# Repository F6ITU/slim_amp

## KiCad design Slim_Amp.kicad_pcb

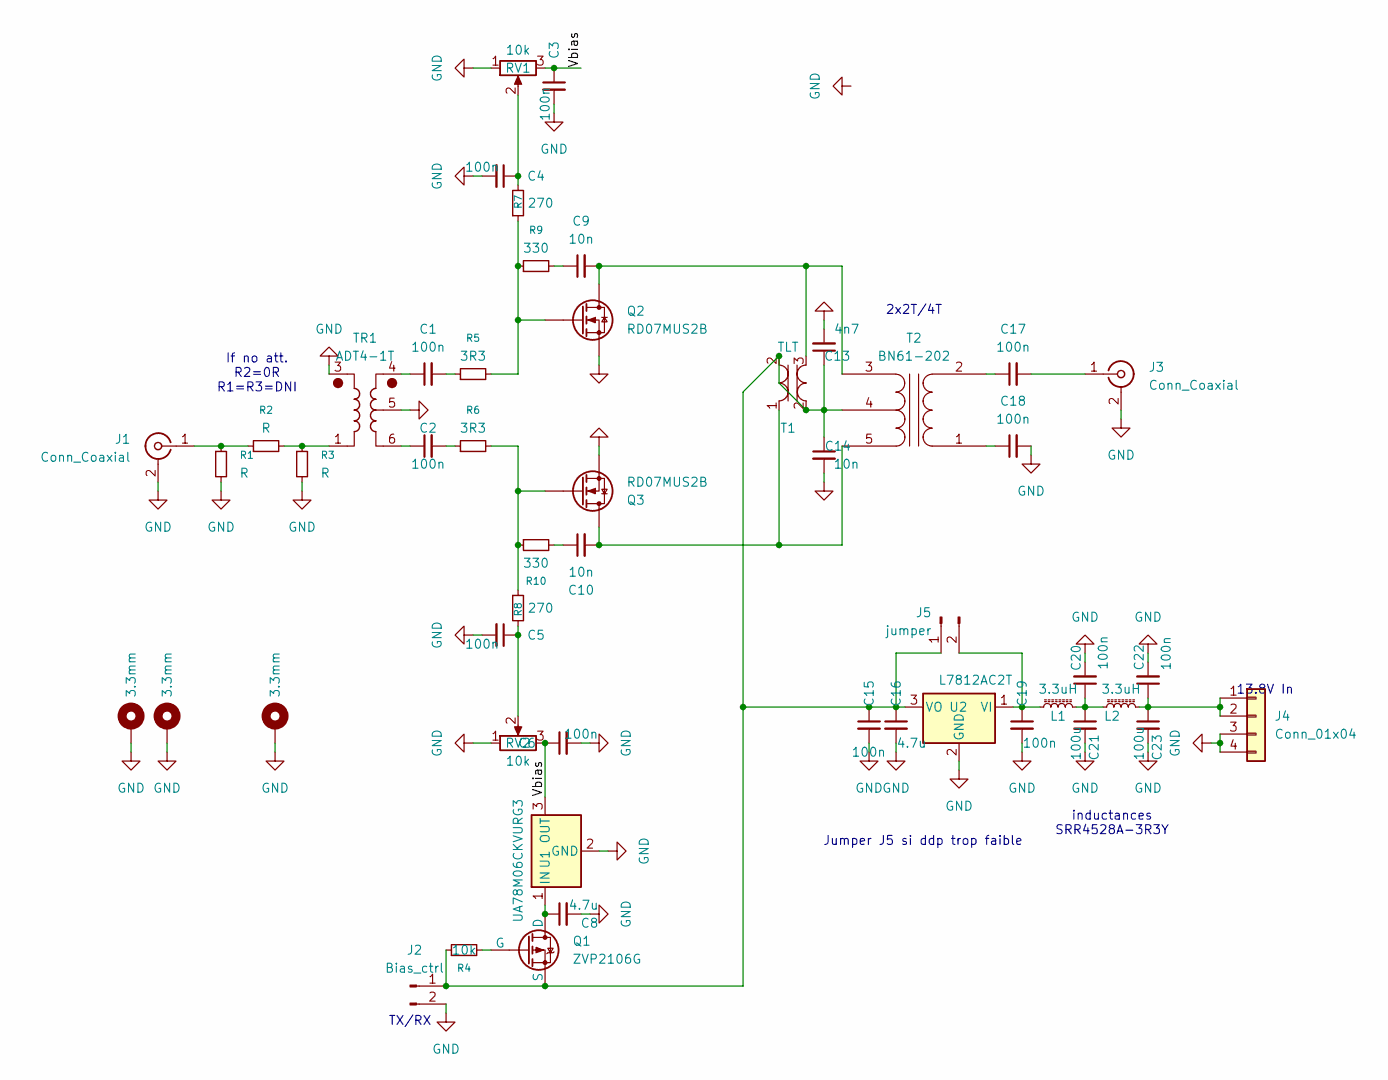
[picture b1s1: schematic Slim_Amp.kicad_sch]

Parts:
C1, C2, C3, C4, C5, C6, C15, C17, C18, C19, C20, C22: 100n; C_1206_3216Metric_Pad1.33x1.80mm_HandSolder
C8, C16: 4.7u; CP_EIA-3216-18_Kemet-A_HandSolder
C9, C10, C14: 10n; C_1206_3216Metric_Pad1.33x1.80mm_HandSolder
C13: 4n7; C_1206_3216Metric_Pad1.33x1.80mm_HandSolder
C21, C23: 100u; CP_Elec_10x14.3
H3, H4, H5: 3.3mm; MountingHole_3.2mm_M3_Pad_Via
J1, J3: Conn_Coaxial; SMA_PINS
J2: Bias_ctrl; Molex_KK-254_AE-6410-02A_1x02_P2.54mm_Vertical
J4: Conn_01x04; Molex_KK-254_AE-6410-04A_1x04_P2.54mm_Vertical
J5: jumper; Molex_KK-254_AE-6410-02A_1x02_P2.54mm_Vertical
L1, L2: 3.3uH; SRR4528A
Q1: ZVP2106G; SOT-223-3_TabPin2
Q2, Q3: RD07MUS2B; RD07M
R1, R2, R3: R; R_0805_2012Metric_Pad1.20x1.40mm_HandSolder
R4: 10k; R_0805_2012Metric_Pad1.20x1.40mm_HandSolder
R5, R6: 3R3; R_0805_2012Metric_Pad1.20x1.40mm_HandSolder
R7, R8: 270; R_0805_2012Metric_Pad1.20x1.40mm_HandSolder
R9, R10: 330; R_1206_3216Metric_Pad1.30x1.75mm_HandSolder
RV1, RV2: 10k; Potentiometer_Bourns_3214W_Vertical
T1: TLT; BN-43-2402
T2: BN61-202; BN-61-202
TR1: ADT4-1T; Mini-Circuits_CD542_H2.84mm
U1: UA78M06CKVURG3; TO-252-3_TabPin2
U2: L7812AC2T; TO-263-3_TabPin2

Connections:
/Vbias: C3.1, C6.1, RV1.3, RV2.3, U1.3 (OUT)
GND: C3.2, C4.2, C5.2, C6.2, C8.2, C13.2, C14.2, C15.2, C16.2, C18.2, C19.2, C20.2, C21.2, C22.2, C23.2, H3.1 (1_1), H4.1 (1_1), H5.1 (1_1), J1.2 (Ext), J2.2, J3.2 (Ext), J4.3, J4.4, Q2.2 (S), Q3.2 (S), R1.2, R3.2, RV1.1, RV2.1, TR1.3, TR1.5, U1.2 (GND), U2.2 (GND)
unnamed: C1.1, TR1.4
unnamed: C1.2, R5.1
unnamed: C2.1, TR1.6
unnamed: C2.2, R6.1
unnamed: C4.1, R7.2, RV1.2
unnamed: C5.1, R8.2, RV2.2
unnamed: C9.1, R9.2
unnamed: C10.1, R10.2
unnamed: C20.1, C21.1, L1.1, L2.2
unnamed: J1.1 (In), R1.1, R2.1
unnamed: C13.1, C14.1, C15.1, C16.1, J2.1, J5.1, Q1.3 (S), R4.1, T1.2 (AA), T2.4 (SC), U2.3 (VO)
unnamed: C17.2, J3.1 (In)
unnamed: C22.1, C23.1, J4.1, J4.2, L2.1
unnamed: C19.1, J5.2, L1.2, U2.1 (VI)
unnamed: C8.1, Q1.1 (D), U1.1 (IN)
unnamed: Q1.2 (G), R4.2
unnamed: C9.2, Q2.1 (D), T1.3 (SB), T2.3 (SA)
unnamed: Q2.3 (G), R5.2, R7.1, R9.1
unnamed: C10.2, Q3.1 (D), T1.1 (AB), T2.5 (SB)
unnamed: Q3.3 (G), R6.2, R8.1, R10.1
unnamed: R2.2, R3.1, TR1.1
unnamed: C18.1, T2.1 (AA)
unnamed: C17.1, T2.2 (AB)

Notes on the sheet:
13.8V In
If no att. R2=0R R1=R3=DNI
inductances SRR4528A-3R3Y
TX/RX
2x2T/4T
Jumper J5 si ddp trop faible

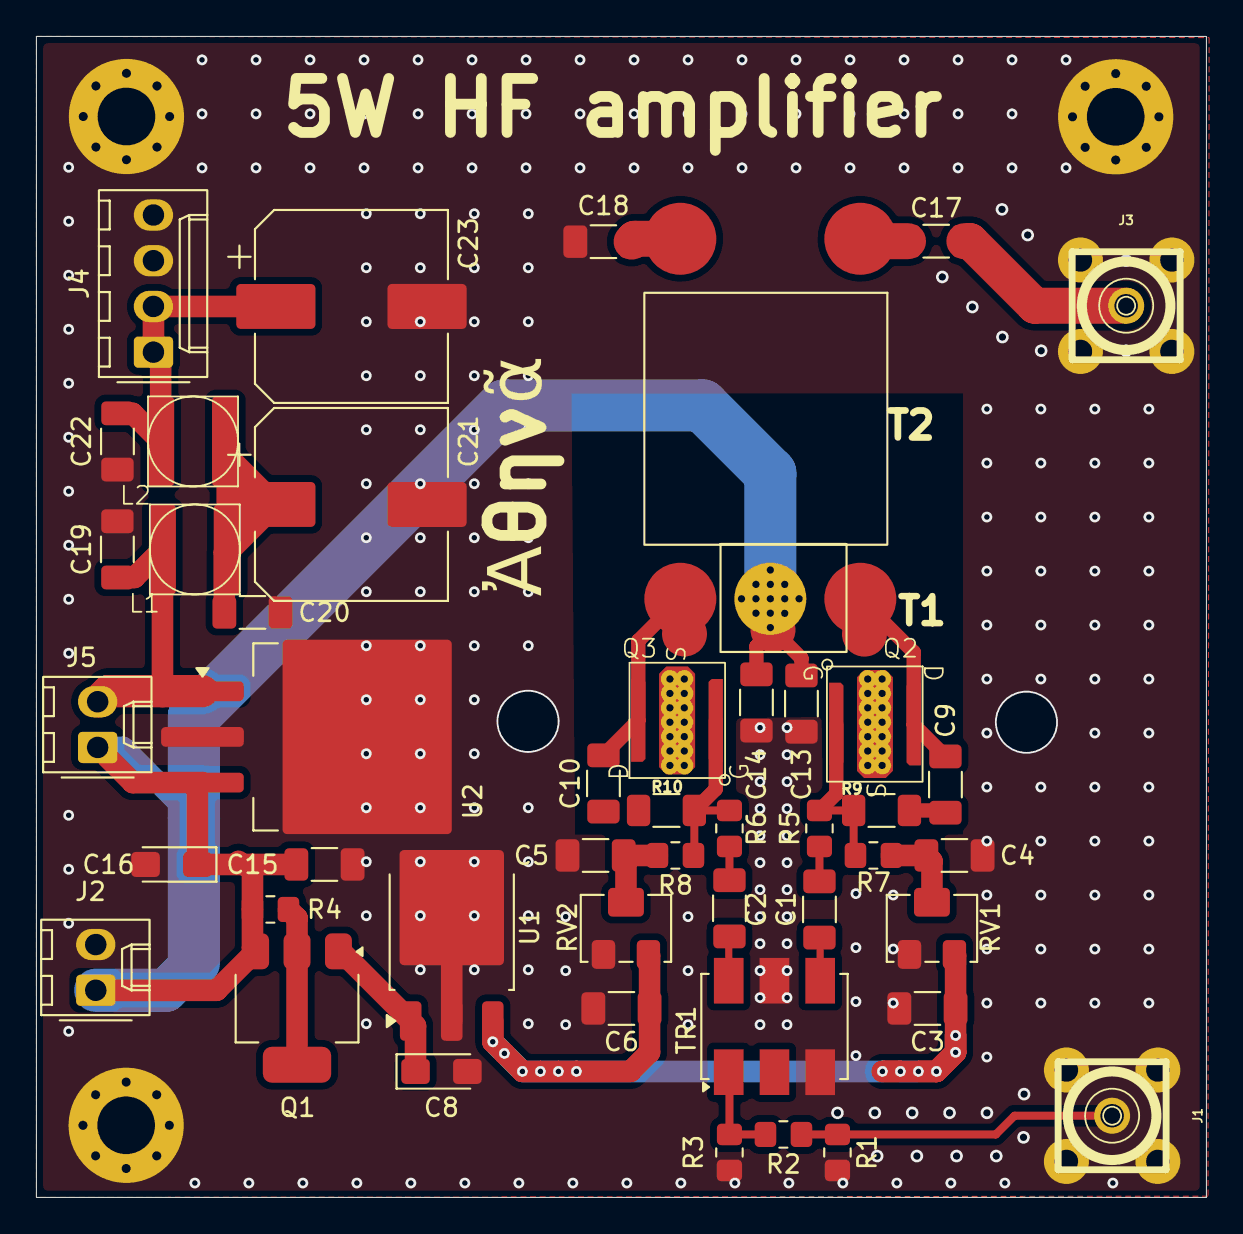
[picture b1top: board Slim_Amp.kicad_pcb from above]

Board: 4 copper layers, 65.0 x 64.5 mm, 50 parts (0 on the bottom side), 25 nets.

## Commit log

2026-06-02 second commit
2026-06-02 third commit
2026-06-02 one more commit
